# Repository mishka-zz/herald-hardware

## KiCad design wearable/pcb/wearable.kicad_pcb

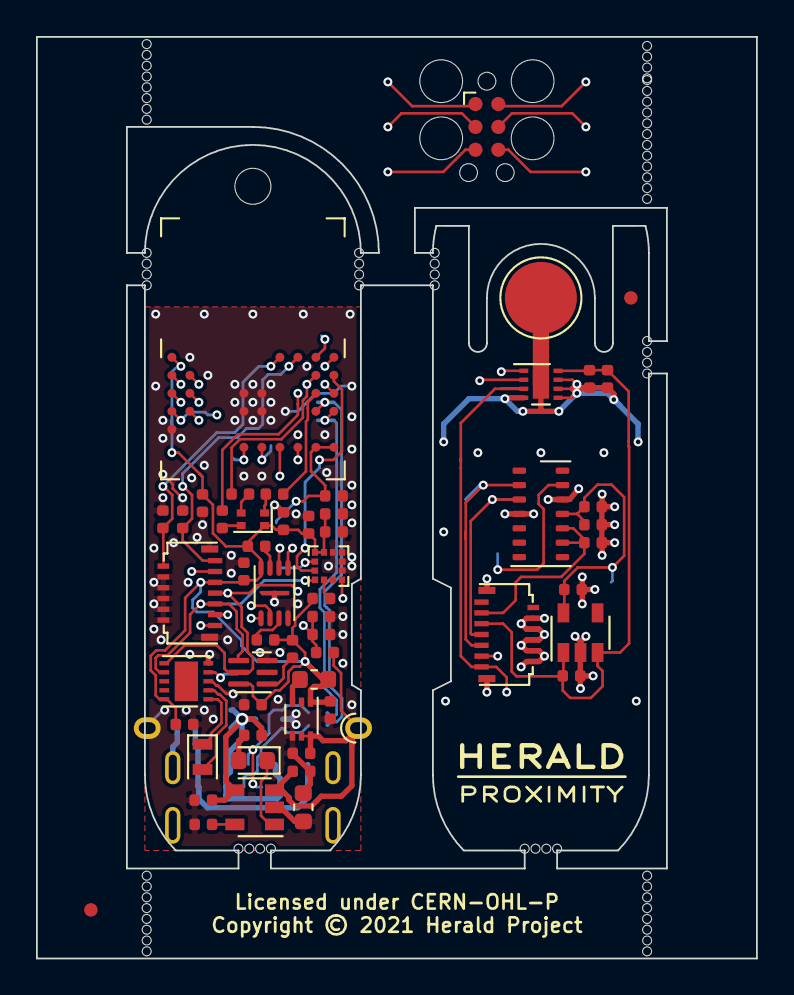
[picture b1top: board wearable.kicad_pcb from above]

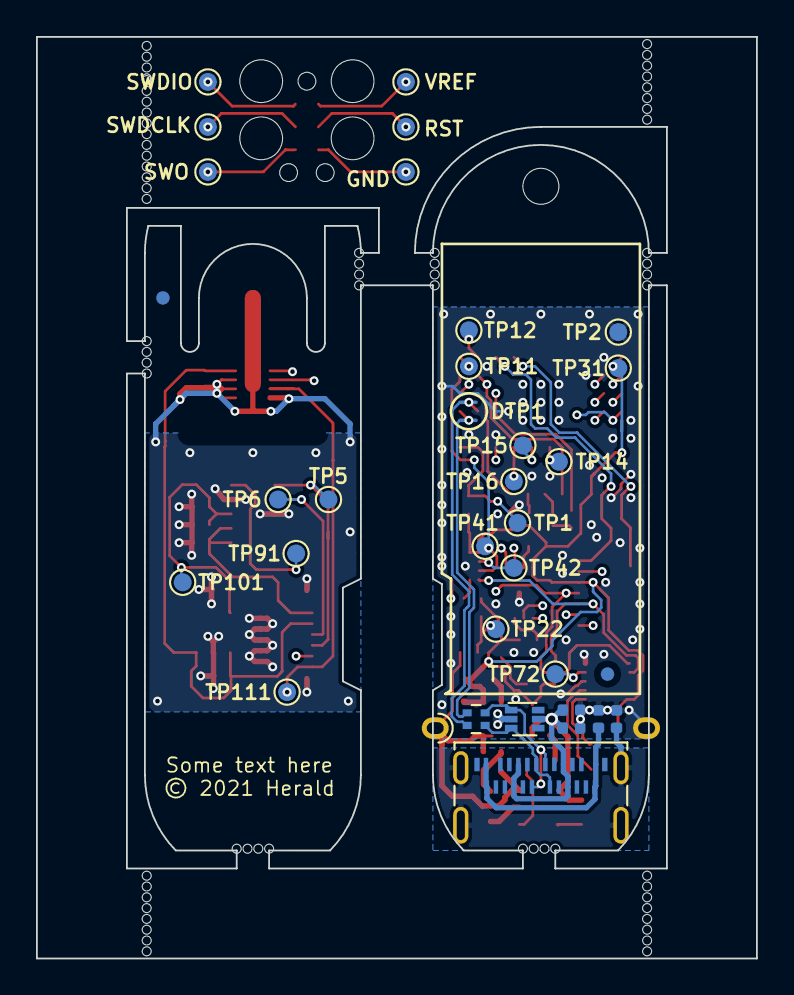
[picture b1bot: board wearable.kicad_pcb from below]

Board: 4 copper layers, 40.0 x 51.2 mm, 90 parts (33 on the bottom side), 55 nets.

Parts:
BT1: LiPo; Herald_Battery_Solder_Pads
C1, C11, C12, C21, C22, C112: 4.7uF; C_0402_1005Metric
C2: 100nF/100V; C_0402_1005Metric
C3, C31, C32, C41, C91, C93: 10uF; C_0402_1005Metric
C13, C14: Tune; C_0402_1005Metric
C23: 10nF; C_0402_1005Metric
C42, C43, C61, C71, C92, C111: 100nF; C_0402_1005Metric
C51, C101, C102: 1uF; C_0402_1005Metric
D1: LED_ARBG; LED_Kingbright_APHF1608
D2: CHSTAT; LED_0603_1608Metric
FB1, FB2: 120R/0.6A; L_0402_1005Metric
FID1, FID2, FID3, FID4: Fiducial; Fiducial_0.75mm_Mask1.5mm
H1: MountingHole; MountingHole_2mm
H2: ThermalSlot; MillSlot_8.0x1.0mm
J1: USB_C_Receptacle_USB2.0; USB_C_Receptacle_IPxx
J2, J3: Extension; TE_1-2328724-3_2Rows_13Pins_P0.3mm_Horizontal
J4: TagConnect; Tag-Connect_TC2030-IDC-FP_2x03_P1.27mm_Vertical
L31: 2.2uH; L_0603_1608Metric
R1, R2, R3, R22: Tune; R_0402_1005Metric
R4: 0 Ohm; R_0603_1608Metric
R21, R41, R51, R61, R62: 10k; R_0402_1005Metric
R23: 6.8M; R_0402_1005Metric
R24: 10M; R_0402_1005Metric
RN1: 22R; R_Array_Convex_2x0402
TP1: VBUS; TestPoint_Pad_D1.0mm
TP2: GND; TestPoint_Pad_D1.0mm
TP5: SCL; TestPoint_Pad_D1.0mm
TP6: SDA; TestPoint_Pad_D1.0mm
TP11: SWDIO; TestPoint_Pad_D1.0mm
TP12: SWDCLK; TestPoint_Pad_D1.0mm
TP14: MISO; TestPoint_Pad_D1.0mm
TP15: MOSI; TestPoint_Pad_D1.0mm
TP16: SCLK; TestPoint_Pad_D1.0mm
TP22: BTSTAT; TestPoint_Pad_D1.0mm
TP31: VDD; TestPoint_Pad_D1.0mm
TP41: ACCINT1; TestPoint_Pad_D1.0mm
TP42: ACCINT2; TestPoint_Pad_D1.0mm
TP72: RTCINT; TestPoint_Pad_D1.0mm
TP91: BIOINT; TestPoint_Pad_D1.0mm
TP101: 1V8; TestPoint_Pad_D1.0mm
TP111: TMPINT; TestPoint_Pad_D1.0mm
TP112: ThPad; TestPoint_Pad_D4.0mm
TP401, TP402, TP403, TP404, TP405, TP406: TestPoint; TestPoint_Pad_D1.0mm
U1: BC833; Fanstel_BC833x
U2: MCP73832-2-OT; SOT-23-5
U3: S-85S1A; SNT-6A
U4: LIS2DE12; LGA-12_2x2mm_P0.5mm
U5: APDS-9250; Broadcom_DFN-6_2x2mm_P0.65mm
U6: MX25R8035FZxxx0; USON-8-1EP_2x3mm_P0.5mm_EP0.25x1.65mm
U7: PCF85063ATL; DFN-10-1EP_2.6x2.6mm_P0.5mm_EP1.25x2.15mm
U8: DT1446-04V; SOT-563
U9: MAX30102; Maxim_OLGA-14_3.3x5.6mm_P0.8mm
U10: TCR3UFxxA; SOT-23-5
U11: TMP1075; WSON-8-1EP_2x2mm_P0.5mm_EP0.9x1.6mm
Y71: 32.768kHz; Crystal_SMD_2012-2Pin_2.0x1.2mm

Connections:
+1V8: C91.1, C92.1, C102.1, TP101.1, U9.11, U10.5
+BATT: BT1.1, C22.2, C31.1, J2.11, R23.1, U2.3, U3.5, U3.6
/Core Board/ACC_INT1: TP41.1, U1.17, U4.12
/Core Board/ACC_INT2: TP42.1, U1.4, U4.11
/Core Board/BIO_INT: J2.3, U1.2
/Core Board/BT_STAT: C23.1, R23.2, R24.1, TP22.1, U1.6
/Core Board/CH_STAT: D2.1, U2.1
/Core Board/FLASH_CS: U1.7, U6.1
/Core Board/FLASH_RST: R61.2, U6.7
/Core Board/FLASH_WP: R62.2, U6.3
/Core Board/LED_B: R1.1, U1.21
/Core Board/LED_G: R2.1, U1.16
/Core Board/LED_R: R3.1, U1.20
/Core Board/LS_INT: R51.2, U5.4
/Core Board/MISO: TP14.1, U1.9, U6.2
/Core Board/MOSI: TP15.1, U1.10, U6.5
/Core Board/NFC1: C13.1, J2.13, U1.23
/Core Board/NFC2: C14.1, J2.12, U1.24
/Core Board/RTC_INT: TP72.1, U1.3, U7.4
/Core Board/SCL: J2.5, U1.12, U4.1, U5.1, U7.7
/Core Board/SCLK: TP16.1, U1.11, U6.6
/Core Board/SDA: J2.7, U1.8, U4.4, U5.2, U7.6
/Core Board/SWDCLK: TP12.1, U1.22
/Core Board/SWDIO: TP11.1, U1.18
/Core Board/USB_D+: RN1.4, U1.19
/Core Board/USB_D-: RN1.3, U1.15
/Extension Board/BIO_INT: J3.11, TP91.1, U9.13
/Extension Board/SCL: J3.9, TP5.1, U9.2, U11.2
/Extension Board/SDA: J3.7, TP6.1, U9.3, U11.1
/Extension Board/TC_GND: J4.5, TP405.1
/Extension Board/TC_RESET: J4.3, TP403.1
/Extension Board/TC_SWDCLK: J4.4, TP404.1
/Extension Board/TC_SWDIO: J4.2, TP402.1
/Extension Board/TC_SWO: J4.6, TP406.1
/Extension Board/TC_VREF: J4.1, TP401.1
/Extension Board/TMP_INT: J3.13, TP111.1, U11.3
Earth: FB1.1, J1.S1
GND: BT1.2, C1.1, C2.1, C3.2, C11.2, C12.2, C13.2, C14.2, C21.1, C22.1, C23.2, C31.2, C32.2, C41.2, C42.2, C43.2, C51.2, C61.1, C71.2, FB1.2, FB2.2, J2.2, J2.4, J2.6, J2.8, J2.10, J2.MP, R4.1, R4.2, R21.2, R24.2, TP2.1, U1.5, U1.25, U1.26, U1.27, U1.28, U2.2, U3.2, U3.4, U4.5, U4.6, U4.7, U4.8, U5.6, U6.4, U6.EP, U7.3, U7.5, U8.2
GND1: C91.2, C92.2, C93.2, C101.2, C102.2, C111.1, C112.1, J3.4, J3.6, J3.8, J3.10, J3.12, J3.MP, TP112.1, U9.4, U9.12, U10.2, U11.4, U11.5, U11.6, U11.7, U11.9
GNDPWR: FB2.1, J1.A1, J1.A12, J1.B1, J1.B12
unnamed: D1.2, R3.2
unnamed: D1.3, R1.2
unnamed: D1.4, R2.2
unnamed: D2.2, R22.1
unnamed: J1.A6, J1.B6, RN1.1, U8.3
unnamed: J1.A7, J1.B7, RN1.2, U8.1
unnamed: L31.2, U3.3
unnamed: R21.1, U2.5
unnamed: R41.2, U4.2
unnamed: U7.1, Y71.1
unnamed: U7.2, Y71.2
VBUS: C1.2, C2.2, C11.1, C21.2, J1.A4, J1.A9, J1.B4, J1.B9, R22.2, TP1.1, U1.13, U1.14, U2.4, U8.5
VDD: C3.1, C12.1, C32.1, C41.1, C42.1, C43.1, C51.1, C61.2, C71.1, D1.1, J2.9, L31.1, R41.1, R51.1, R61.1, R62.1, TP31.1, U1.1, U3.1, U4.9, U4.10, U5.3, U6.8, U7.10
VDD1: C101.1, C111.2, C112.2, J3.5, U10.1, U10.3, U11.8
Vdrive: C93.1, J3.3, U9.9, U9.10

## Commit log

2021-05-30 The very first prototype, panelized.

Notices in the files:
wearable/pcb/wearable.kicad_pcb:
© 2021 Herald Project Contributors
Licensed under CERN-OHL-P version 2
Copyright © 2021 Herald Project
© 2021 Herald
